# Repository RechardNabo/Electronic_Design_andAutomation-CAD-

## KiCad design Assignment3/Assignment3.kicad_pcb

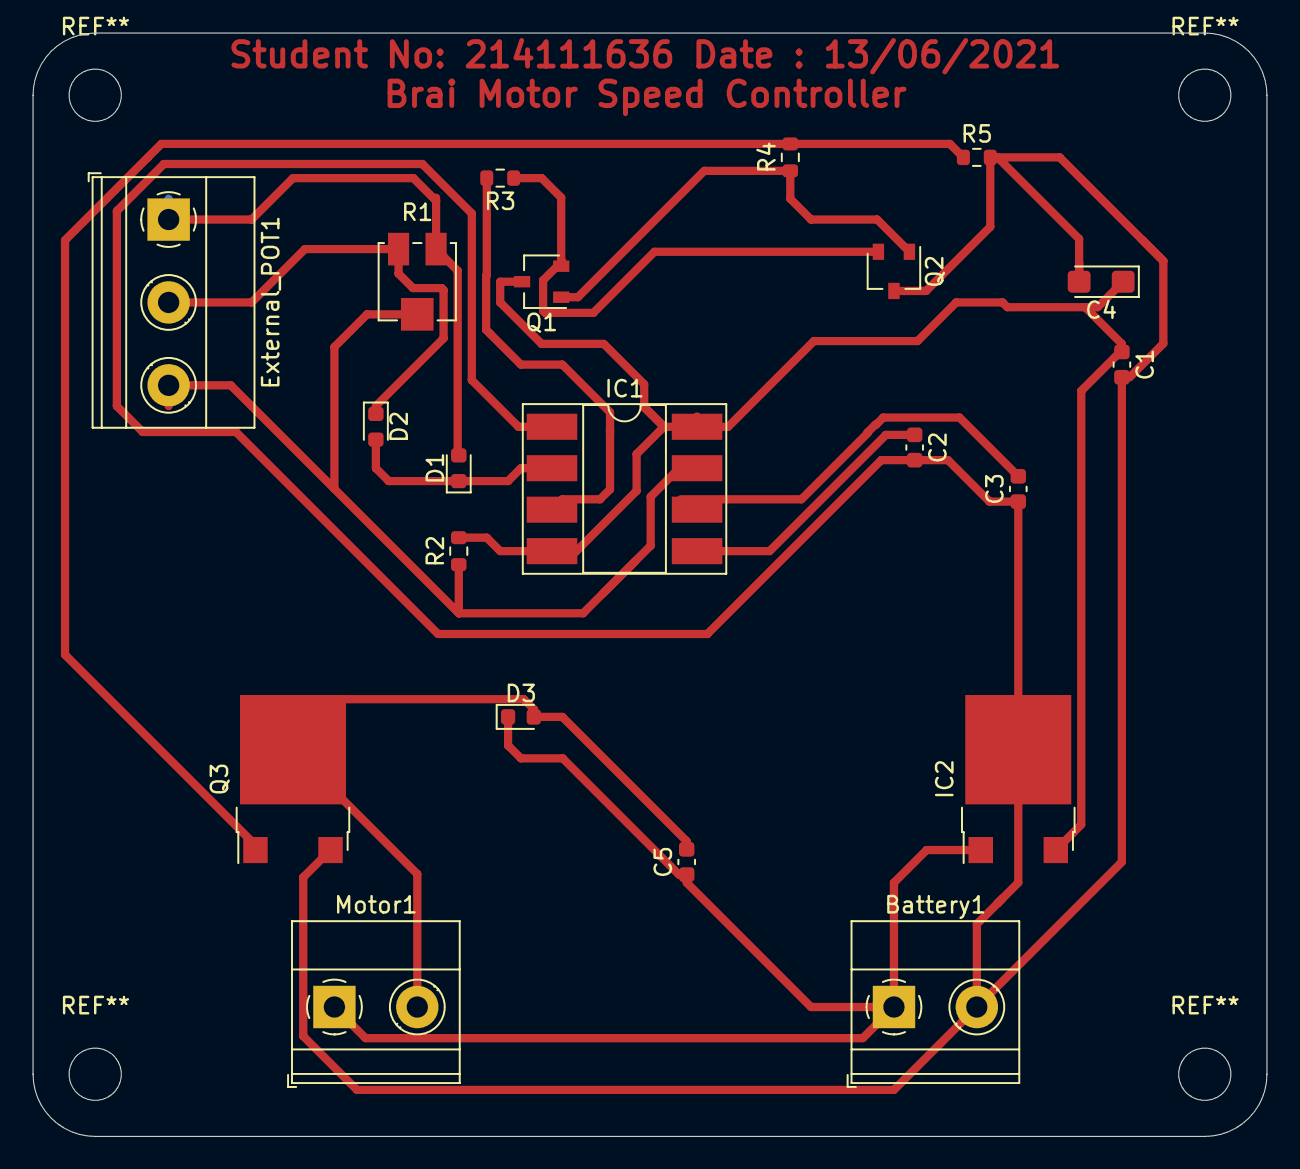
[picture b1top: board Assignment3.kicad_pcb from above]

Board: 2 copper layers, 75.6 x 67.6 mm, 21 parts (0 on the bottom side), 13 nets.

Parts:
Battery1: Battery; TerminalBlock_Phoenix_MKDS-1,5-2-5.08_1x02_P5.08mm_Horizont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
C1, C2, C3, C5: 100n; C_0603_1608Metric
C4: 10uf / 35V; CP_EIA-3216-10_Kemet-I
D1, D2: 1N4148; D_0603_1608Metric
D3: 1N4004; D_0603_1608Metric
External_POT1: External_POT; TerminalBlock_Phoenix_MKDS-1,5-3-5.08_1x03_P5.08mm_Horizont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
IC1: LM555N; DIP-8_W8.89mm_SMDSocket_LongPads
IC2: L7809; ATPAK-2
Motor1: Motor; TerminalBlock_Phoenix_MKDS-1,5-2-5.08_1x02_P5.08mm_Horizont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
Q1: 2N3904; SOT-23W
Q2: 2N3906; SOT-23W
Q3: IRLZ44N; ATPAK-2
R1: 100k; Potentiometer_Bourns_3314J_Vertical
R2, R5: 10k; R_0603_1608Metric
R3: 2.2k; R_0603_1608Metric
R4: 22; R_0603_1608Metric

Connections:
0: Battery1.2, C1.2, C2.2, C3.1, C4.2, IC1.1, IC2.2, Q2.3, Q3.3, R5.2
+9V: C1.1, C4.1, IC1.4, IC1.8, IC2.3, Q1.3, R2.2
unnamed: Battery1.1, C5.1, D3.1, IC2.1, Motor1.1
unnamed: C2.1, IC1.5
unnamed: C3.2, D1.1, D2.2, IC1.2, IC1.6
unnamed: C5.2, D3.2, Motor1.2, Q3.2
unnamed: D1.2, External_POT1.1, R1.1
unnamed: D2.1, External_POT1.2, R1.3
unnamed: External_POT1.3, IC1.7, R1.2, R2.1
unnamed: IC1.3, R3.2
unnamed: Q1.1, Q2.1, R4.1
unnamed: Q1.2, Q2.2, R3.1
unnamed: Q3.1, R4.2, R5.1
